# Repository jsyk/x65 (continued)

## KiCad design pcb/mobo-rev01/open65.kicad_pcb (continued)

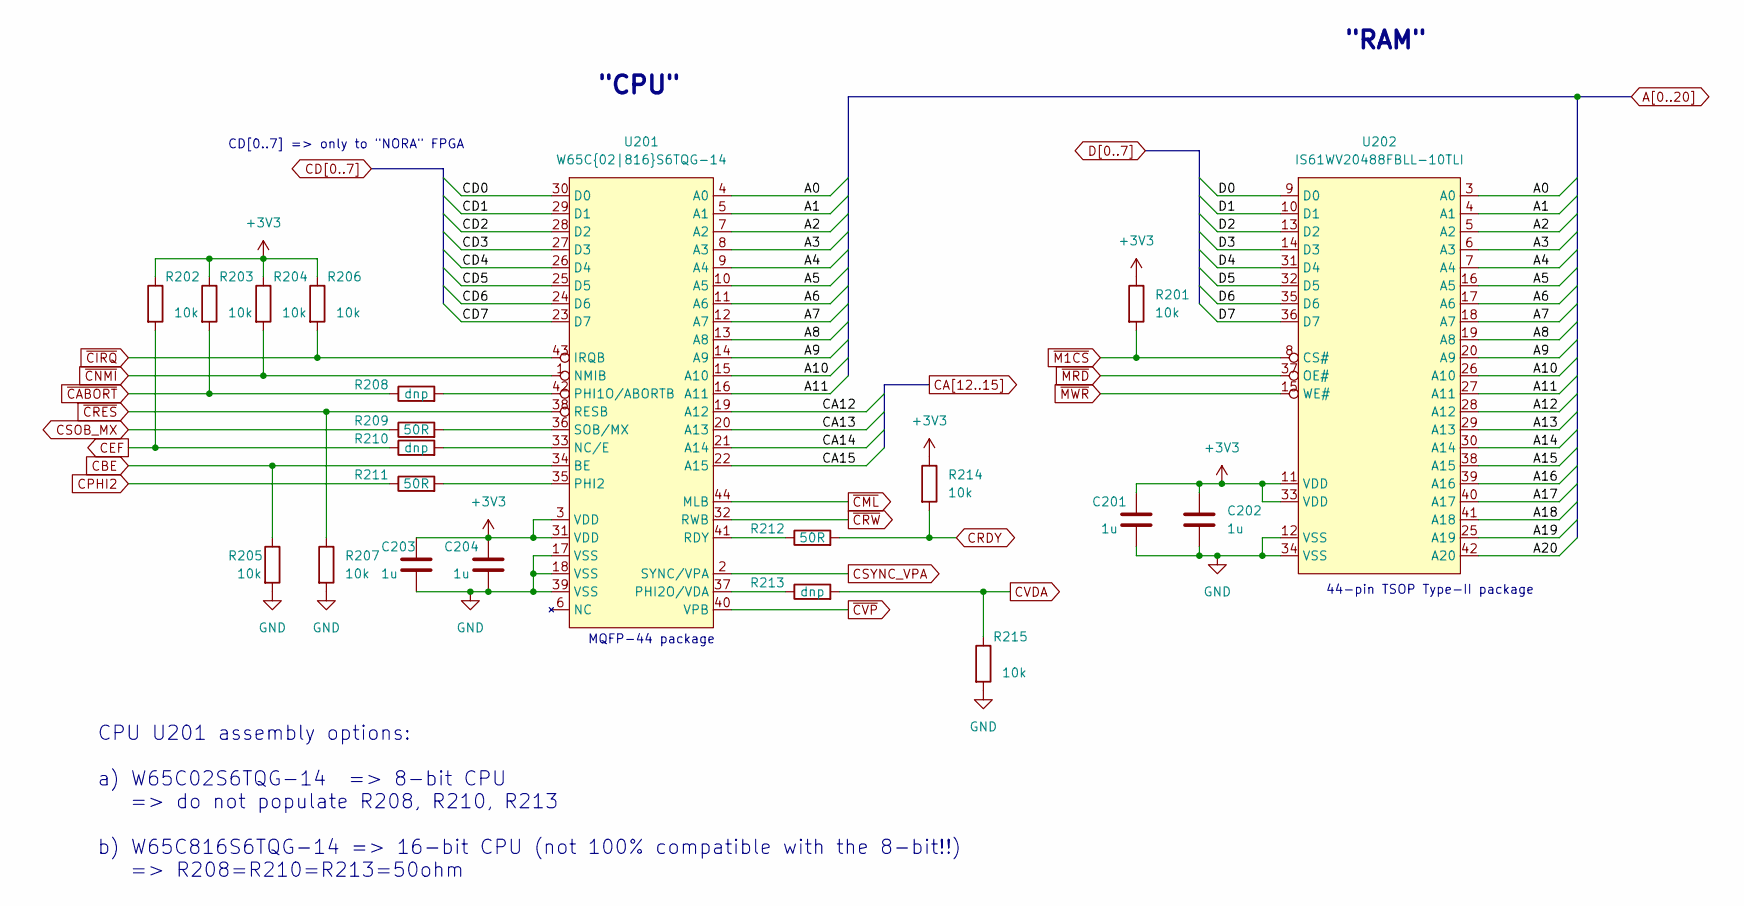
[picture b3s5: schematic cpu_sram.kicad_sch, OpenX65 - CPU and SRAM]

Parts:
C201, C202, C203, C204: 1u; C_0603_1608Metric_Pad1.08x0.95mm_HandSolder
R201, R202, R203, R204, R205, R206, R207, R214, R215: 10k; R_0603_1608Metric_Pad0.98x0.95mm_HandSolder
R208, R210, R213: dnp; R_0603_1608Metric_Pad0.98x0.95mm_HandSolder
R209, R211, R212: 50R; R_0603_1608Metric_Pad0.98x0.95mm_HandSolder
U201: W65C{02|816}S6TQG-14; MQFP-44_10x10mm_P0.8mm
U202: IS61WV20488FBLL-10TLI; TSOP-II-44_10.16x18.41mm_P0.8mm

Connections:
+3V3: C201.1, C202.1, C203.1, C204.1, R201.1, R202.1, R203.1, R204.1, R206.1, R214.1, U201.3 (VDD), U201.31 (VDD), U202.11 (VDD), U202.33 (VDD); also elsewhere on the board
A0: U201.4 (A0), U202.3 (A0); also elsewhere on the board
A1: U201.5 (A1), U202.4 (A1); also elsewhere on the board
A2: U201.7 (A2), U202.5 (A2); also elsewhere on the board
A3: U201.8 (A3), U202.6 (A3); also elsewhere on the board
A4: U201.9 (A4), U202.7 (A4); also elsewhere on the board
A5: U201.10 (A5), U202.16 (A5); also elsewhere on the board
A6: U201.11 (A6), U202.17 (A6); also elsewhere on the board
A7: U201.12 (A7), U202.18 (A7); also elsewhere on the board
A8: U201.13 (A8), U202.19 (A8); also elsewhere on the board
A9: U201.14 (A9), U202.20 (A9); also elsewhere on the board
A10: U201.15 (A10), U202.26 (A10); also elsewhere on the board
A11: U201.16 (A11), U202.27 (A11); also elsewhere on the board
A12: U202.28 (A12); also elsewhere on the board
A13: U202.29 (A13); also elsewhere on the board
A14: U202.30 (A14); also elsewhere on the board
A15: U202.38 (A15); also elsewhere on the board
A16: U202.39 (A16); also elsewhere on the board
A17: U202.40 (A17); also elsewhere on the board
A18: U202.41 (A18); also elsewhere on the board
A19: U202.25 (A19); also elsewhere on the board
A20: U202.42 (A20); also elsewhere on the board
CA12: U201.19 (A12); also elsewhere on the board
CA13: U201.20 (A13); also elsewhere on the board
CA14: U201.21 (A14); also elsewhere on the board
CA15: U201.22 (A15); also elsewhere on the board
CBE: R205.1, U201.34 (BE); also elsewhere on the board
CD0: U201.30 (D0); also elsewhere on the board
CD1: U201.29 (D1); also elsewhere on the board
CD2: U201.28 (D2); also elsewhere on the board
CD3: U201.27 (D3); also elsewhere on the board
CD4: U201.26 (D4); also elsewhere on the board
CD5: U201.25 (D5); also elsewhere on the board
CD6: U201.24 (D6); also elsewhere on the board
CD7: U201.23 (D7); also elsewhere on the board
CEF: R202.2, R210.1; also elsewhere on the board
CPHI2: R211.1; also elsewhere on the board
CRDY: R212.2, R214.2; also elsewhere on the board
CSOB_MX: R209.1; also elsewhere on the board
CSYNC_VPA: U201.2 (SYNC/VPA); also elsewhere on the board
CVDA: R213.2, R215.1; also elsewhere on the board
D0: U202.9 (D0); also elsewhere on the board
D1: U202.10 (D1); also elsewhere on the board
D2: U202.13 (D2); also elsewhere on the board
D3: U202.14 (D3); also elsewhere on the board
D4: U202.31 (D4); also elsewhere on the board
D5: U202.32 (D5); also elsewhere on the board
D6: U202.35 (D6); also elsewhere on the board
D7: U202.36 (D7); also elsewhere on the board
GND: C201.2, C202.2, C203.2, C204.2, R205.2, R207.2, R215.2, U201.17 (VSS), U201.18 (VSS), U201.39 (VSS), U202.12 (VSS), U202.34 (VSS); also elsewhere on the board
unnamed: R208.2, U201.42 (PHI1O/ABORTB)
unnamed: R209.2, U201.36 (SOB/MX)
unnamed: R210.2, U201.33 (NC/E)
unnamed: R211.2, U201.35 (PHI2)
unnamed: R212.1, U201.41 (RDY)
unnamed: R213.1, U201.37 (PHI2O/VDA)
~CABORT: R203.2, R208.1; also elsewhere on the board
~CIRQ: R206.2, U201.43 (IRQB); also elsewhere on the board
~CML: U201.44 (MLB); also elsewhere on the board
~CNMI: R204.2, U201.1 (NMIB); also elsewhere on the board
~CRES: R207.1, U201.38 (RESB); also elsewhere on the board
~CRW: U201.32 (RWB); also elsewhere on the board
~CVP: U201.40 (VPB); also elsewhere on the board
~M1CS: R201.2, U202.8 (CS#); also elsewhere on the board
~MRD: U202.37 (OE#); also elsewhere on the board
~MWR: U202.15 (WE#); also elsewhere on the board

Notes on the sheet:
CD[0..7] => only to "NORA" FPGA
"CPU"
CPU U201 assembly options: a) W65C02S6TQG-14 => 8-bit CPU => do not populate R208, R210, R213 b) W65C816S6TQG-14 => 16-bit CPU (not 100% compatible with the 8-bit!!) => R208=R210=R213=50ohm
44-pin TSOP Type-II package
MQFP-44 package
"RAM"

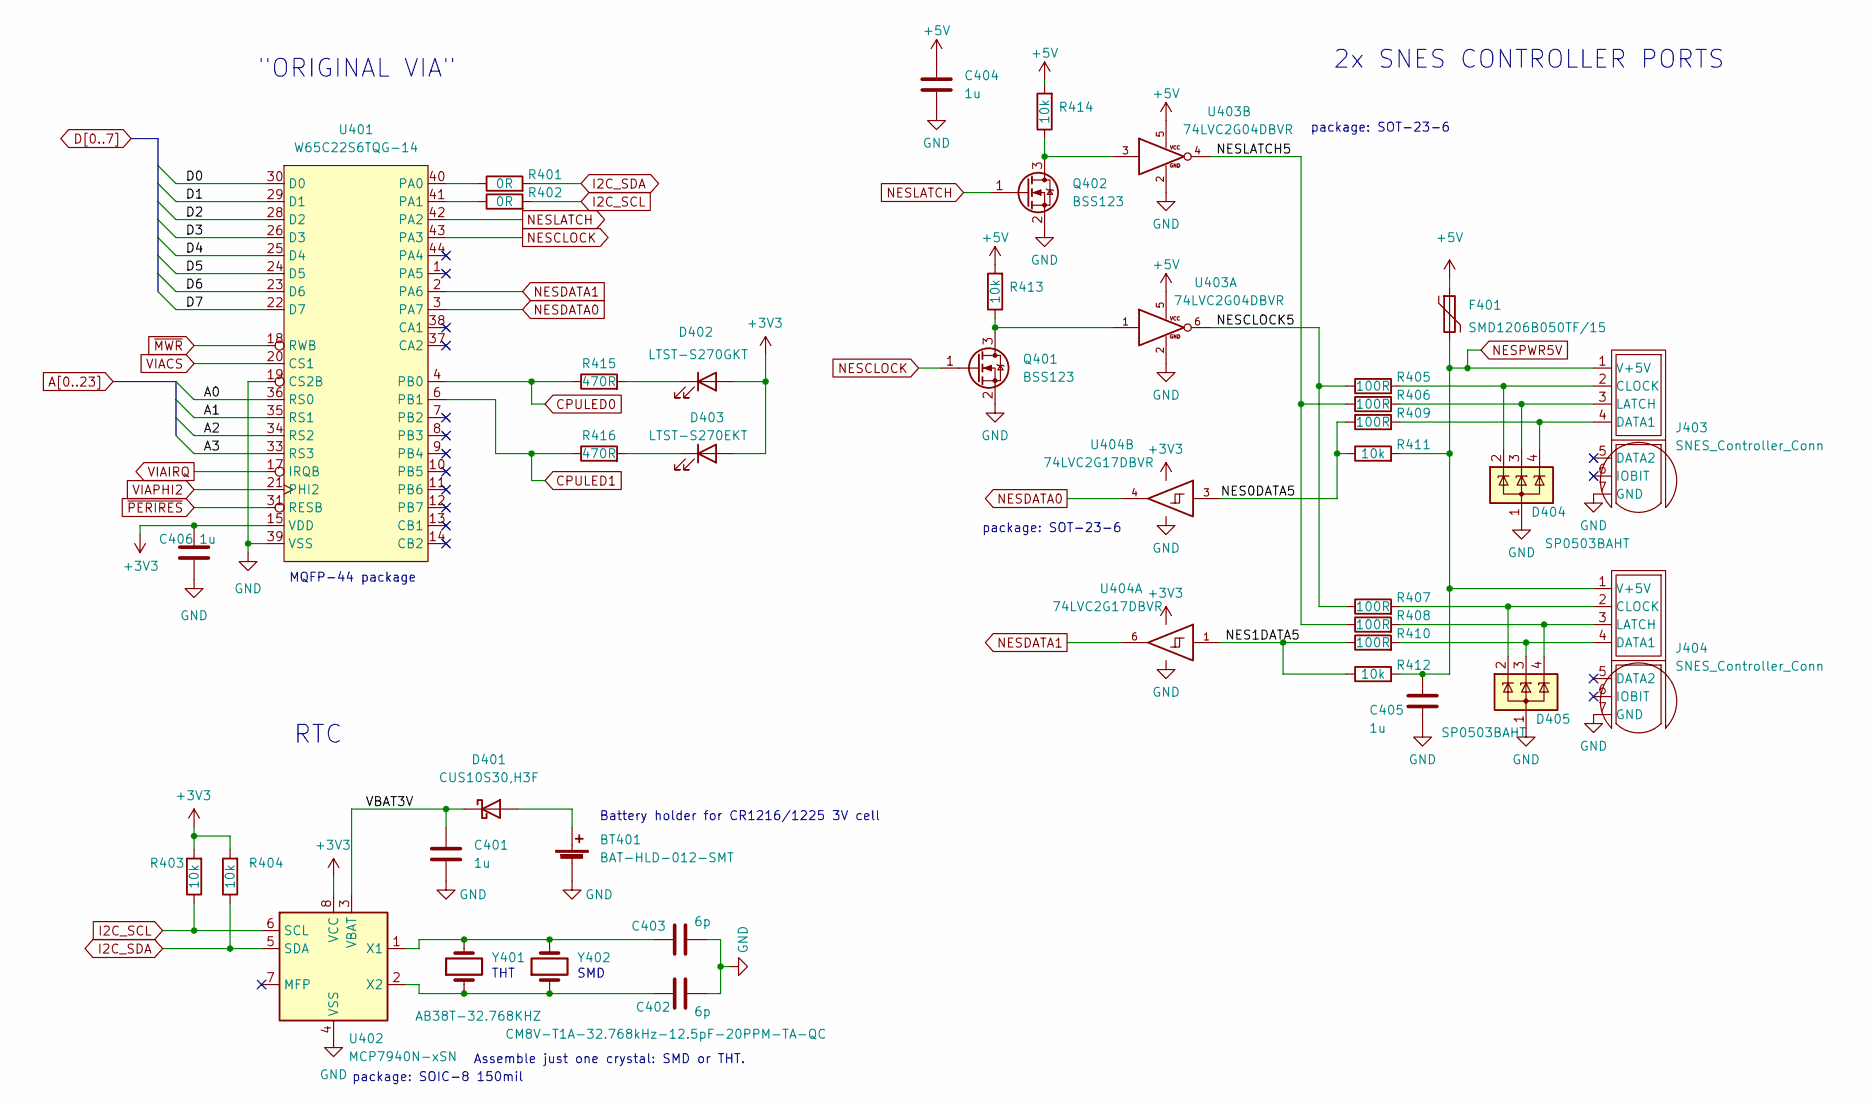
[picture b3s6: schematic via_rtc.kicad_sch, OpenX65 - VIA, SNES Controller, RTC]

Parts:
BT401: BAT-HLD-012-SMT; BatteryHolder_LINX_BAT-HLD-012-SMT
C401, C404, C405, C406: 1u; C_0603_1608Metric_Pad1.08x0.95mm_HandSolder
C402, C403: 6p; C_0603_1608Metric_Pad1.08x0.95mm_HandSolder
D401: CUS10S30,H3F; D_SOD-323_HandSoldering
D402: LTST-S270GKT; LED_0603_1608Metric_Pad1.05x0.95mm_HandSolder
D403: LTST-S270EKT; LED_0603_1608Metric_Pad1.05x0.95mm_HandSolder
D404, D405: SP0503BAHT; SOT-143
F401: SMD1206B050TF/15; Fuse_1206_3216Metric_Pad1.42x1.75mm_HandSolder
J403, J404: SNES_Controller_Conn; SNES_Controller_Conn_7p_90deg_P1Left
Q401, Q402: BSS123; SOT-23
R401, R402: 0R; R_0603_1608Metric_Pad0.98x0.95mm_HandSolder
R403, R404, R411, R412, R413, R414: 10k; R_0603_1608Metric_Pad0.98x0.95mm_HandSolder
R405, R406, R407, R408, R409, R410: 100R; R_0603_1608Metric_Pad0.98x0.95mm_HandSolder
R415, R416: 470R; R_0603_1608Metric_Pad0.98x0.95mm_HandSolder
U401: W65C22S6TQG-14; MQFP-44_10x10mm_P0.8mm
U402: MCP7940N-xSN; SO-8_3.9x4.9mm_P1.27mm
U403: 74LVC2G04DBVR; SOT-23-6_Handsoldering
U404: 74LVC2G17DBVR; SOT-23-6_Handsoldering
Y401: AB38T-32.768KHZ; Crystal_C38-LF_D3.0mm_L8.0mm_Horizontal
Y402: CM8V-T1A-32.768kHz-12.5pF-20PPM-TA-QC; Crystal_SMD_MicroCrystal_CC8V-T1A-2Pin_2.0x1.2mm_HandSolder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

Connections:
+3V3: C406.1, D402.2 (A), D403.2 (A), R403.2, R404.2, U401.15 (VDD), U402.8 (VCC), U404.5 (VCC); also elsewhere on the board
+5V: C404.1, F401.1, R413.2, R414.2, U403.5; also elsewhere on the board
/VIA, RTC, SNES/NES0DATA5: R409.1, R411.1, U404.3
/VIA, RTC, SNES/NES1DATA5: R410.1, R412.1, U404.1
/VIA, RTC, SNES/NESCLOCK5: R405.1, R407.1, U403.6
/VIA, RTC, SNES/NESLATCH5: R406.1, R408.1, U403.4
/VIA, RTC, SNES/VBAT3V: C401.1, D401.1 (K), U402.3 (VBAT)
A0: U401.36 (RS0); also elsewhere on the board
A1: U401.35 (RS1); also elsewhere on the board
A2: U401.34 (RS2); also elsewhere on the board
A3: U401.33 (RS3); also elsewhere on the board
CPULED0: R415.1, U401.4 (PB0); also elsewhere on the board
CPULED1: R416.1, U401.6 (PB1); also elsewhere on the board
D0: U401.30 (D0); also elsewhere on the board
D1: U401.29 (D1); also elsewhere on the board
D2: U401.28 (D2); also elsewhere on the board
D3: U401.26 (D3); also elsewhere on the board
D4: U401.25 (D4); also elsewhere on the board
D5: U401.24 (D5); also elsewhere on the board
D6: U401.23 (D6); also elsewhere on the board
D7: U401.22 (D7); also elsewhere on the board
GND: BT401.2 (-), C401.2, C402.2, C403.2, C404.2, C405.2, C406.2, D404.1 (A), D405.1 (A), J403.7 (GND), J404.7 (GND), Q401.2 (S), Q402.2 (S), U401.19 (CS2B), U401.39 (VSS), U402.4 (VSS), U403.2, U404.2 (GND); also elsewhere on the board
I2C_SCL: R402.2, R403.1, U402.6 (SCL); also elsewhere on the board
I2C_SDA: R401.2, R404.1, U402.5 (SDA); also elsewhere on the board
NESCLOCK: Q401.1 (G), U401.43 (PA3); also elsewhere on the board
NESDATA0: U401.3 (PA7), U404.4; also elsewhere on the board
NESDATA1: U401.2 (PA6), U404.6; also elsewhere on the board
NESLATCH: Q402.1 (G), U401.42 (PA2); also elsewhere on the board
NESPWR5V: C405.1, F401.2, J403.1 (V+5V), J404.1 (V+5V), R411.2, R412.2; also elsewhere on the board
unnamed: BT401.1 (+), D401.2 (A)
unnamed: C402.1, U402.2 (X2), Y401.1, Y402.1
unnamed: C403.1, U402.1 (X1), Y401.2, Y402.2
unnamed: D402.1 (K), R415.2
unnamed: D403.1 (K), R416.2
unnamed: D404.2 (K), J403.2 (CLOCK), R405.2
unnamed: D404.3 (K), J403.3 (LATCH), R406.2
unnamed: D404.4 (K), J403.4 (DATA1), R409.2
unnamed: D405.2 (K), J404.2 (CLOCK), R407.2
unnamed: D405.3 (K), J404.4 (DATA1), R410.2
unnamed: D405.4 (K), J404.3 (LATCH), R408.2
unnamed: Q401.3 (D), R413.1, U403.1
unnamed: Q402.3 (D), R414.1, U403.3
unnamed: R401.1, U401.40 (PA0)
unnamed: R402.1, U401.41 (PA1)
VIACS: U401.20 (CS1); also elsewhere on the board
VIAIRQ: U401.17 (IRQB); also elsewhere on the board
VIAPHI2: U401.21 (PHI2); also elsewhere on the board
~MWR: U401.18 (RWB); also elsewhere on the board
~PERIRES: U401.31 (RESB); also elsewhere on the board

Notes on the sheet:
RTC
SMD
MQFP-44 package
"ORIGINAL VIA"
Assemble just one crystal: SMD or THT.
2x SNES CONTROLLER PORTS
package: SOT-23-6
Battery holder for CR1216/1225 3V cell
package: SOIC-8 150mil
THT

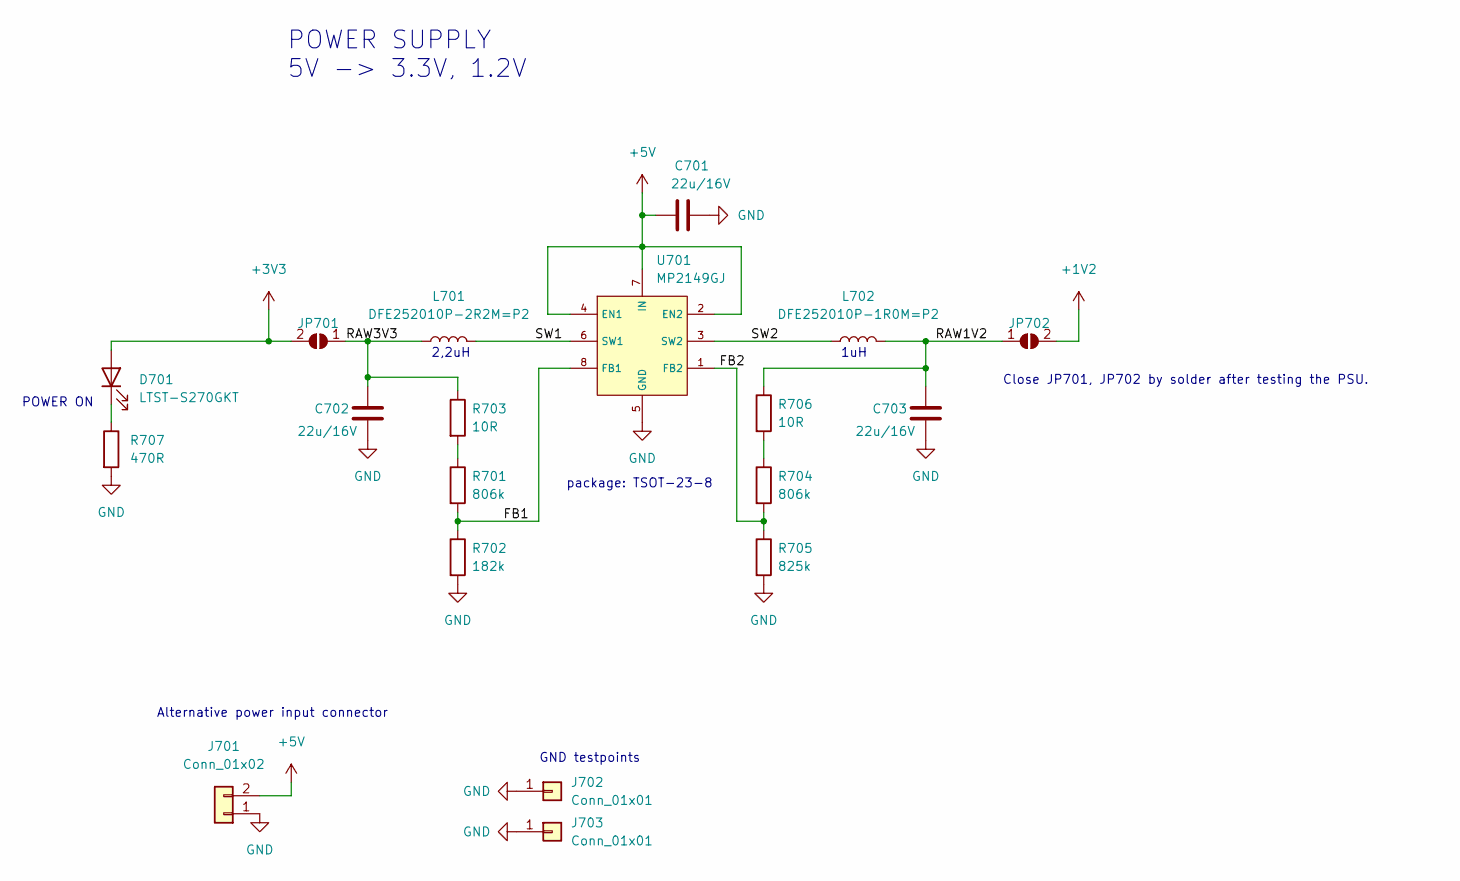
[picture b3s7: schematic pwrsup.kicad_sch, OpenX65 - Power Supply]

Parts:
C701, C702, C703: 22u/16V; C_0805_2012Metric_Pad1.18x1.45mm_HandSolder
D701: LTST-S270GKT; LED_0603_1608Metric_Pad1.05x0.95mm_HandSolder
J701: Conn_01x02; PinHeader_1x02_P2.54mm_Vertical
J702, J703: Conn_01x01; PinHeader_1x01_P2.54mm_Vertical
JP701, JP702: SolderJumper_2_Bridged; SolderJumper-2_P1.3mm_Open_RoundedPad1.0x1.5mm
L701: DFE252010P-2R2M=P2; L_1008_2520Metric_Pad1.43x2.20mm_HandSolder
L702: DFE252010P-1R0M=P2; L_1008_2520Metric_Pad1.43x2.20mm_HandSolder
R701, R704: 806k; R_0603_1608Metric_Pad0.98x0.95mm_HandSolder
R702: 182k; R_0603_1608Metric_Pad0.98x0.95mm_HandSolder
R703, R706: 10R; R_0603_1608Metric_Pad0.98x0.95mm_HandSolder
R705: 825k; R_0603_1608Metric_Pad0.98x0.95mm_HandSolder
R707: 470R; R_0603_1608Metric_Pad0.98x0.95mm_HandSolder
U701: MP2149GJ; TSOT-23-8_HandSoldering

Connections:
+1V2: JP702.2 (B); also elsewhere on the board
+3V3: D701.2 (A), JP701.2 (B); also elsewhere on the board
+5V: C701.1, J701.2, U701.2 (EN2), U701.4 (EN1), U701.7 (IN); also elsewhere on the board
/Power Supply/FB1: R701.2, R702.1, U701.8 (FB1)
/Power Supply/FB2: R704.2, R705.1, U701.1 (FB2)
/Power Supply/RAW1V2: C703.2, JP702.1 (A), L702.2, R706.1
/Power Supply/RAW3V3: C702.2, JP701.1 (A), L701.1, R703.1
/Power Supply/SW1: L701.2, U701.6 (SW1)
/Power Supply/SW2: L702.1, U701.3 (SW2)
GND: C701.2, C702.1, C703.1, J701.1, J702.1, J703.1, R702.2, R705.2, R707.2, U701.5 (GND); also elsewhere on the board
unnamed: D701.1 (K), R707.1
unnamed: R701.1, R703.2
unnamed: R704.1, R706.2

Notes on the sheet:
1uH
2,2uH
POWER ON
POWER SUPPLY 5V -> 3.3V, 1.2V
GND testpoints
package: TSOT-23-8
Close JP701, JP702 by solder after testing the PSU.
Alternative power input connector

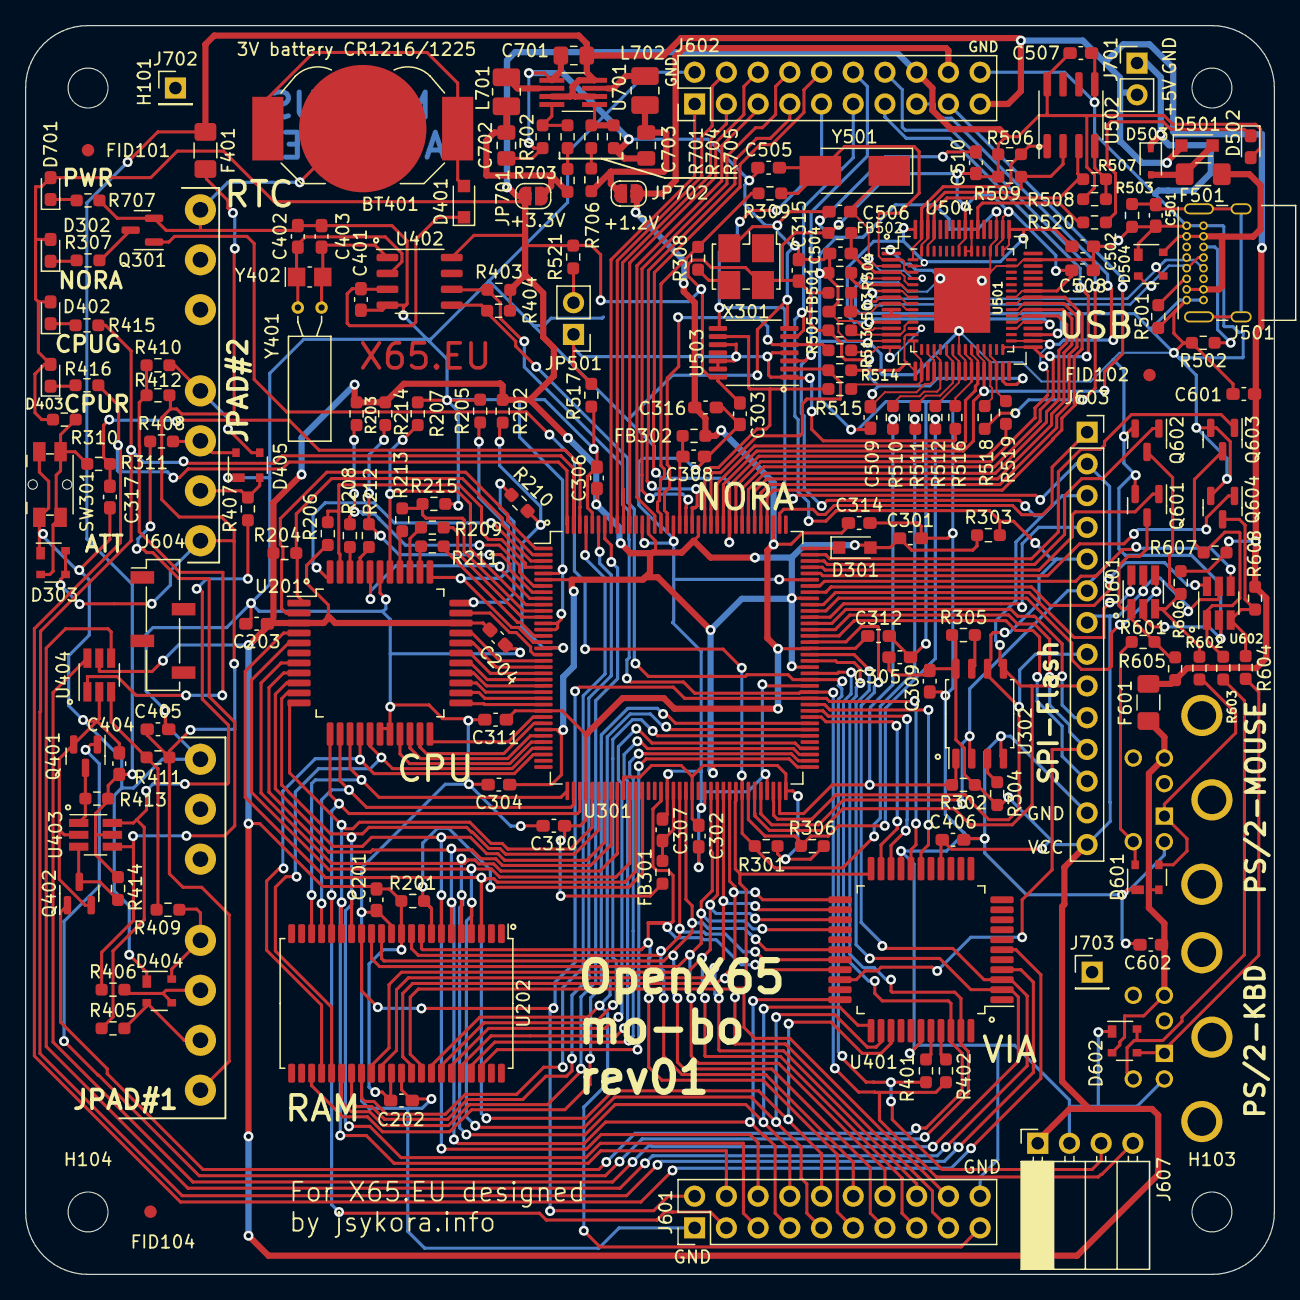
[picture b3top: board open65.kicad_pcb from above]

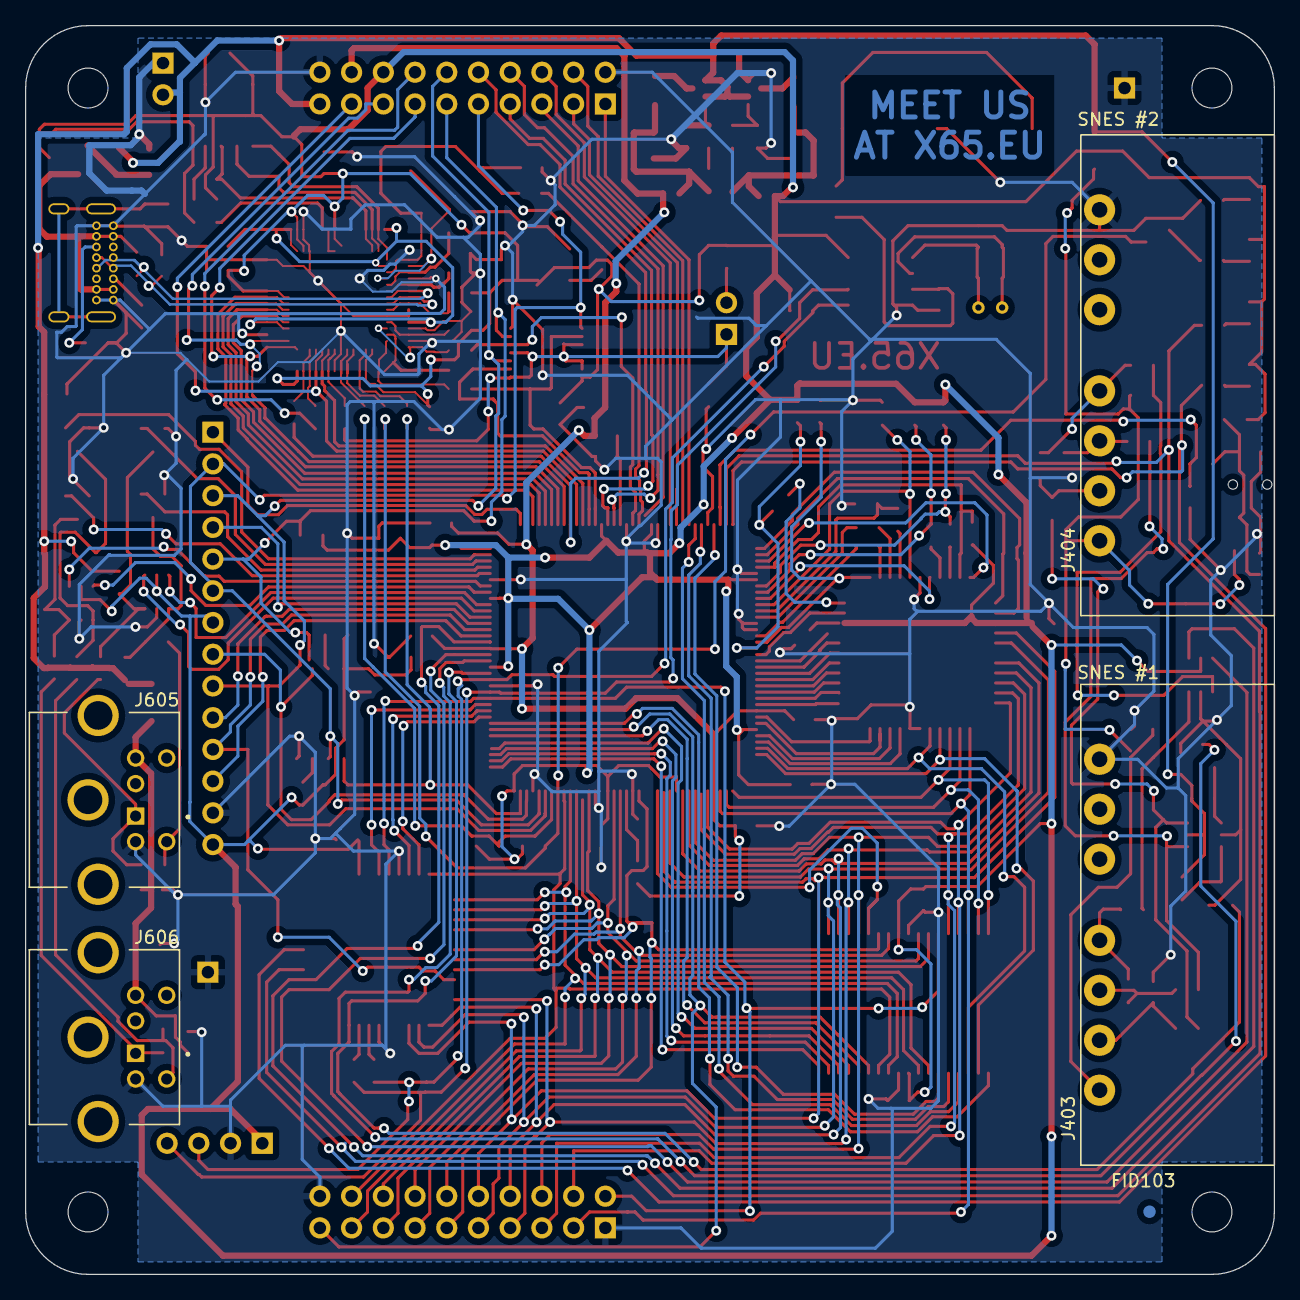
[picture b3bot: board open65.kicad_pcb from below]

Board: 2 copper layers, 100.0 x 100.0 mm, 195 parts (5 on the bottom side), 199 nets.

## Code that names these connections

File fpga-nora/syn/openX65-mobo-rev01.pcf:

# OpenX65 motherboard rev 01

#
# Bank 3
#   Pins 1 - 34
#
set_io CSYNC_VPA    1
set_io CNMIn        2
set_io CMLn         3
set_io CIRQn        4
set_io CABORTn      7
set_io CRDY         8
set_io CVPn         9
set_io CRESn        10
set_io CVDA         11
set_io CSOB_MX      12
set_io CPHI2        15
set_io CBE          16
set_io CEF          17
set_io CRWn         18
set_io CD[0]          19  
set_io CD[1]          20
set_io CD[2]          21
set_io CD[3]          22
set_io CD[4]          23
set_io CD[5]          24
set_io CD[6]          25
set_io CD[7]          26
set_io CA[15]         28
set_io CA[14]         29
set_io CA[13]         31
set_io CA[12]         32
set_io MAL[11]          33
set_io MAL[10]          34

#
# Bank 2
#   Pins 37 - 64
#
set_io MAL[9]           37
set_io MAL[8]           38
set_io MAL[7]           39
set_io MAL[6]           41
set_io MAL[5]           42
set_io MAL[4]           43
set_io MAL[3]           44
set_io MAL[2]           45
set_io MAL[1]           47
set_io MAL[0]           48
set_io M1CSn        49
set_io MD[0]           52
set_io MD[1]           55
set_io MD[2]           56
set_io MD[3]           60
set_io MD[4]           61
set_io MD[5]           62
set_io MD[6]           63
set_io MD[7]           64


#
# Bank 1
#   Pins 73 - 107
#
set_io MAH[20]          73
set_io MAH[18]          74
set_io MAH[17]          75
set_io MAH[16]          76
set_io MAH[15]          78
set_io MRDn         79
set_io MAH[19]          80
#set_io VIAPHI2      81
#set_io VIACS        82
#set_io VIAIRQ       83
set_io MWRn         84
set_io I2C_SCL      85
set_io I2C_SDA      87
set_io NESLATCH     88
set_io NESCLOCK     90
set_io NESDATA1     91
set_io NESDATA0     93
set_io ILICSn       94
set_io PERIRESn     95
set_io ILIDC        96
set_io TCSn         97
set_io PS2M_DATA    98
set_io PS2M_CLK     99
set_io PS2K_CLK     101
set_io PS2K_DATA    102
set_io PS2K_DATADR  104
set_io PS2M_CLKDR   105
set_io PS2M_DATADR  106
set_io PS2K_CLKDR   107

#
# Bank 0
#   Pins 110 - 144
#
set_io CPUTYPE02    110
set_io UART_CTS     112
set_io UART_RTS     113
set_io UART_TX      114
set_io UART_RX      115
set_io VERADONE     116
set_io VERARSTn     117
set_io VERAFCSn     118
set_io ICD2VERAROM  119
set_io ICD_CSn      120
set_io ICD_MOSI     121
set_io ICD_MISO     122
set_io VCS2n        124
set_io VIRQn        125
set_io ICD_SCK      128
set_io FPGACLK      129
set_io VCS1n        130
set_io AUDIO_LRCK   134
set_io VCS0n        135
set_io AUDIO_DATA   136
set_io AUDIO_BCK    137
set_io MAH[12]          138
set_io MAH[13]          139
set_io MAH[14]          141
set_io ATTBTN       142
set_io CPULED0      143
set_io CPULED1      144


#
# Bank SPI
#
set_io FMOSI        67
set_io FMISO        68
set_io FSCK         70
set_io FLASHCSn     71

# set_io CDONE        65

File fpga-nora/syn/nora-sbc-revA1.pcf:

# X65 SBC rev.A1

#
# Bank 3
#   Pins 1 - 34
#
set_io CSYNC_VPA    1
set_io CNMIn        2
set_io CMLn         3
set_io CIRQn        4
set_io CABORTn      7
set_io CRDY         8
set_io CVPn         9
set_io CRESn        10
set_io CVDA         11
set_io CSOB_MX      12
set_io CPHI2        15
set_io CBE          16
set_io CEF          17
set_io CRWn         18
set_io CD[0]          19  
set_io CD[1]          20
set_io CD[2]          21
set_io CD[3]          22
set_io CD[4]          23
set_io CD[5]          24
set_io CD[6]          25
set_io CD[7]          26
set_io CA[15]         28
set_io CA[14]         29
set_io CA[13]         31
set_io CA[12]         32
set_io MAL[11]          33
set_io MAL[10]          34

#
# Bank 2
#   Pins 37 - 64
#
set_io MAL[9]           37
set_io MAL[8]           38
set_io MAL[7]           39
set_io MAL[6]           41
set_io MAL[5]           42
set_io MAL[4]           43
set_io MAL[3]           44
set_io MAL[2]           45
set_io MAL[1]           47
set_io MAL[0]           48
set_io M1CSn        49
set_io MD[0]           52
set_io MD[1]           55
set_io MD[2]           56
set_io MD[3]           60
set_io MD[4]           61
set_io MD[5]           62
set_io MD[6]           63
set_io MD[7]           64


#
# Bank 1
#   Pins 73 - 107
#
set_io MAH[20]          73
set_io MAH[18]          74
set_io MAH[17]          75
set_io MAH[16]          76
set_io MAH[15]          78
set_io MRDn             79
set_io MAH[19]          80
set_io UE_IRQn          81
set_io PS2M_DATA        82
set_io PS2M_CLK         83
set_io MWRn         84
set_io I2C_SCL      85
set_io I2C_SDA      87
set_io EIRQn        88
set_io AIRQn        90
set_io VIRQn        91
set_io ACS1n        93
set_io VCS0n        94
set_io UE_CS3n      95
set_io UE_SCK       96
set_io UE_CSn       97
set_io UE_MISO      98
set_io UE_MOSI      99
set_io UE_SCL       101
set_io UE_SDA       102
set_io UE_TXD       104
set_io UE_RXD       105
set_io PS2K_DATA    106
set_io PS2K_CLK     107

#
# Bank 0
#   Pins 110 - 144
#
set_io CPUTYPE02    110
set_io UART_RTS     112
set_io UART_CTS     113
set_io UART_TX      114
set_io UART_RX      115
set_io VEAURADONE   116
set_io VERARSTn     117
set_io ERSTn        118
set_io ARSTn        119
set_io ICD_CSn      120
set_io ICD_MOSI     121
set_io ICD_MISO     122
set_io ECS2n        124
set_io DIPLED0      125
set_io ICD_SCK      128
set_io FPGACLK      129
set_io NESDATA0     130
set_io NESDATA1     134
set_io NESCLOCK     135
set_io NESLATCH     136
set_io DIPLED1      137
set_io MAH[12]          138
set_io MAH[13]          139
set_io MAH[14]          141
set_io ATTBTN       142
set_io CPULED0      143
set_io CPULED1      144


#
# Bank SPI
#
set_io FMOSI        67
set_io FMISO        68
set_io FSCK         70
set_io FLASHCSn     71

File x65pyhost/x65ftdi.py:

import pyftdi.spi

# Documenation pyftdi: SPI API
# https://eblot.github.io/pyftdi/api/spi.html

class X65Ftdi:
    # Definitions of pins of the FTDI FT2232H in the OpenX65 motherboard.
    # // bit masks of the signals on ADBUSx (low byte)
    PIN_SCK  = 0x0001
    PIN_MOSI = 0x0002
    PIN_MISO = 0x0004
    PIN_NORAFCSN = 0x0010         # // ADBUS4 (GPIOL0) (FLASHCSN)
    PIN_NORADONE = 0x0040           # // ADBUS6 (GPIOL2)
    PIN_NORARSTN = 0x0080         # // ADBUS7 (GPIOL3)
    # // bit masks of the signals on ACBUSx (high byte)
    PIN_ICD2NORAROM = 0x0100			#// ACBUS0
    PIN_ICDCSN = 0x0200			        #// ACBUS1
    PIN_AURARSTN = 0x0400		        #// ACBUS2 (was ICD2VERAROM)
    PIN_AURAFCSN = 0x0800			    #// ACBUS3 (was VERA2FCS)
    PIN_VERAFCSN = 0x1000			    #// ACBUS4
    PIN_CPUTYPE02 = 0x2000              #// ACBUS5
    PIN_VAFCDONE = 0x4000			    #// ACBUS6 (was VERADONE)
    PIN_VERARSTN = 0x8000			    #// ACBUS7

    PINS_ALL = PIN_NORAFCSN | PIN_NORADONE | PIN_NORARSTN | PIN_ICD2NORAROM | PIN_ICDCSN | PIN_AURARSTN | PIN_AURAFCSN | PIN_VERAFCSN | PIN_VAFCDONE | PIN_VERARSTN | PIN_CPUTYPE02

    def __init__(self, url = 'ftdi://ftdi:2232/1', log_file_name=None):
        if url is not None:
            self.openFtdi(url)
        # open log file?
        if log_file_name is not None:
            self.logf = open(log_file_name, 'a')
            self.logf.write('\n\nStart of log\n')
        else:
            self.logf = None

    def openFtdi(self, url = 'ftdi://ftdi:2232/1'):
        # Instantiate a SPI controller
        self.spi = pyftdi.spi.SpiController()

        # Configure the first interface (IF/1) of the first FTDI device as a
        # SPI master
        self.spi.configure(url)

        # Get a SPI port to a SPI slave w/ /CS on A*BUS3 and SPI mode 0 @ 6MHz
        self.slave = self.spi.get_port(cs=0, freq=1E6, mode=0)

        # Get GPIO port to manage extra pins, use A*BUS4 as GPO, A*BUS4 as GPI
        self.gpio = self.spi.get_gpio()

        self.pinout_idle()

    # // configure the high-byte (ACBUSx) to route SPI to the ICD,
    # // and keep ICD high (deselect).
    def pinout_idle(self):
        # for all GPIOs, configure just ICD2NORAROM and ICDCSN as outputs
        self.gpio.set_direction(X65Ftdi.PINS_ALL,
                            X65Ftdi.PIN_ICD2NORAROM | X65Ftdi.PIN_ICDCSN)
        # // drive low ICD2NORAROM (this unroutes SPI to flash),
        # // drive high ICDCSN, all others are IN.
        self.gpio.write(X65Ftdi.PIN_ICDCSN)


    # // ICD chip select assert
    # // should only happen while ICD2NORAROM=Low
    def icd_chip_select(self):
        # // drive low ICD2NORAROM (this unroutes SPI to flash),
        # // drive low ICDCSN to activate the ICD
        self.gpio.write(0)
        if self.logf is not None:
            self.logf.write('SELECT\n')
        # mpsse_set_gpio_high(VERA2FCSN | VERAFCSN | VERADONE | VERARSTN, 
        # 			ICD2NORAROM | ICDCSN);

    # // ICD chip select deassert
    def icd_chip_deselect(self):
        # // drive low ICD2NORAROM (this unroutes SPI to flash),
        # // drive high ICDCSN to de-activate the ICD
        self.gpio.write(X65Ftdi.PIN_ICDCSN)
        if self.logf is not None:
            self.logf.write('DESEL\n')
        # mpsse_set_gpio_high(ICDCSN | VERA2FCSN | VERAFCSN | VERADONE | VERARSTN, 
        # 			ICD2NORAROM | ICDCSN);

    def spiexchange(self, out, readlen):
        if self.logf is not None:
            self.logf.write('  EX.out {}\n'.format( ''.join('{:02x} '.format(x) for x in out) ))
        read = self.slave.exchange(out, readlen, start=False, stop=False, duplex=True)
        if self.logf is not None:
            self.logf.write('  EX.inp {}\n'.format( ''.join('{:02x} '.format(x) for x in read) ))
        return read

    def spiwriteonly(self, out):
        if self.logf is not None:
            self.logf.write('  WO.out {}\n'.format( ''.join('{:02x} '.format(x) for x in out) ))
        self.slave.write(out,  start=False, stop=False)

    # Read the CPUTYPE02 signal available on FTDI pin ACBUS5.
    # Returns TRUE in case of 65C02, and FALSE in case of 65C816 CPU is installed on the target board.
    def is_cputype02(self):
        return (self.gpio.read() & X65Ftdi.PIN_CPUTYPE02) != 0

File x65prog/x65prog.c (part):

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};

// bit masks of the signals on ACBUSx
#define ICD2NORAROM 		0x01			// ACBUS0
#define ICDCSN				0x02			// ACBUS1
#define AURARSTN			0x04			// ACBUS2
#define AURAFCS				0x08			// ACBUS3
#define VERAFCS				0x10			// ACBUS4
#define VERAAURADONE		0x40			// ACBUS6
#define VERARSTN			0x80			// ACBUS7

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	uint8_t direction = 0x03;

	if (!cs_b) {
		// ADBUS4 (GPIOL0) = FLASHCSN for NORA
		direction |= 0x10;		// set to output mode, will drive 0
	}

	if (!creset_b) {
		// ADBUS7 (GPIOL3) = NORARSTN
		direction |= 0x80;		// set to output mode, will drive 0
	}

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static void set_cs_creset_vera(int cs_b, int creset_b)
{
	// bitmap of GPIO output register values (0/1 drive)
	uint8_t gpio = ICD2NORAROM;
	// bitmap of GPIO direction register values (0=in, 1=out)
	uint8_t direction = 0x03 | ICD2NORAROM | VERAFCS | AURAFCS;

	if (!cs_b) {
		// ADBUS4 (GPIOL0) = VERAFCS for VERA
		// direction |= VERAFCS;		// set to output mode, will drive logic 1
		gpio |= VERAFCS;			// drive HIGH to VERAFCS; this enables the bus-switch U404 on VABO
	}

	if (!creset_b) {
		// ADBUS7 (GPIOL3) = VERARSTN
		direction |= VERARSTN;		// set to output mode, will drive 0
	}

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static void set_cs_creset_aura(int cs_b, int creset_b)
{
	// bitmap of GPIO output register values (0/1 drive)
	uint8_t gpio = ICD2NORAROM;				// drive high ICD2NORAROM, so that FTDI gets to FMOSI/FSCK bus
	// bitmap of GPIO direction register values (0=in, 1=out)
	uint8_t direction = 0x03 | ICD2NORAROM | VERAFCS | AURAFCS;		// drive ICD2NORAROM, VERAFCS, AURAFCS

	if (!cs_b) {
		// ACBUS3) = AURAFCS for AURA
		gpio |= AURAFCS;			// drive HIGH to AURAFCS; this enables the bus-switch U602 on VABO
	}

	if (!creset_b) {
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
static bool get_cdone_nora(void)
{
	// ADBUS6 (GPIOL2) = NORADONE
	return (mpsse_readb_low() & 0x40) != 0;
}

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	// drive high ICD2NORAROM (= ICD2FLASHES), ICDCSN, 
	// drive low AURAFCS, low VERAFCS,
	// keep others as IN.
	mpsse_set_gpio_high(ICD2NORAROM | ICDCSN  | VERAAURADONE | VERARSTN, 
				ICD2NORAROM | ICDCSN | AURAFCS | VERAFCS);
}

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{
	// drive low ICD2NORAROM (this unroutes SPI to flash), 
	// drive high ICDCSN, keep others as IN.
	mpsse_set_gpio_high(ICDCSN | AURAFCS | VERAFCS | VERAAURADONE | VERARSTN, 
				ICD2NORAROM | ICDCSN);
}

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
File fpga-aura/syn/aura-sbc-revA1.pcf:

# OpenX65 VABO rev 01 - AURA FPGA pins

set_io      DB[0]       25
set_io      MWRN        23
set_io      DB[2]       27
set_io      DB[1]       26
set_io      VCS0N       28
set_io      DB[3]       31
set_io      DB[4]       32
set_io      DB[5]       34
set_io      DB[7]       37
set_io      ASYSCLK     35
set_io      DB[6]       36
set_io      SD_SSELN    43
set_io      MUTEN       38
set_io      AURALED     42

# set_io      ARSTN       8     # pin 8 cannot be assigned in UL
set_io      IOCSN       47       # unused in SBC
set_io      AUDIO_BCK   9
set_io      VAUDIO_LRCK 10
set_io      VAUDIO_DATA 11
set_io      VAUDIO_BCK  12
set_io      AB[4]       21
set_io      AB[3]       13
set_io      MRDN        20
set_io      AB[2]       19
set_io      AB[1]       18
set_io      ASPI_MOSI   14
set_io      ASPI_MISO   17
set_io      ASPI_SCK    15
set_io      AFLASH_SSELN    16

set_io      ACS1N       46
set_io      AIRQN       48
set_io      AB[0]       45
set_io      AUDIO_LRCK  4
set_io      AUDIO_DATA  3

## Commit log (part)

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2023-04-11 PCB mobo rev01
2023-04-11 x65prog sources
2023-04-11 FPGA NORA files
2023-04-11 Update gitignore with verilog tmp files
2023-04-13 update gitignore
2023-04-13 NORA: correct timing of WR and other signals
2023-04-13 Add testing pictures from the scope
2023-04-18 Started the video/audio board
2023-04-29 start of pythonic ICD
2023-04-30 Add LED-blink x65 program
2023-05-04 PS2 port can read keyboard scan-codes
2023-05-07 x65prog can r/w the VERA Flash
2023-05-07 pyhost: do-vchartest, do-videotest work fine
2023-05-13 Various updates; I2C slave
2023-05-13 Add some photos
2023-05-13 CX16 is READY.
2023-05-14 Add keyboard FIFO -> kbd input works OK
2023-05-14 New photos, update Address Space
2023-05-15 rom: banktest
2023-05-15 Update docs
2023-05-15 smc: implement ps2k cmd send and status report
    problem: bus controller does not update rambank_nr on CPU write!!!
    after unrelated change in the smc!
2023-05-15 fix verilog undefined wires
    yosis reports undefined wires just as warnings, but then the
    output bitstream fails intermitently... what?
2023-05-15 Readme: describe structure
2023-05-18 doc fix
2023-05-18 verilog fix bit width in arithmetic expr.
2023-05-18 smc: fix arith expr bit-length
2023-05-18 smc: localparams, non-working 2B commands (but the x16 rom runs well)
2023-05-21 bus_controller: fix rambank/rombank write cycle position!!
2023-05-21 Photos: front and rear view with connectors
2023-05-25 rename file X16 -> CX16.txt
2023-05-25 split smc into ps2_kbd_host, add a tb
2023-05-25 add UEXT to the ideas for rev02
2023-05-26 rewrite of smc and ps2_kbd_host, to handle the 2B command; CapsLock now works!
2023-05-26 smc: remove commented out code
2023-05-27 do-videotest: run VRAM memtest
2023-06-02 phaser comments
2023-06-10 fpga code cleanup & stabilization
2023-06-20 Update readme & scm with the latest PCB bringup info
2023-06-20 NORA: add mouse support, not tested at all!
2023-06-21 ps2_kbd_host: report RX FIFO count
2023-06-21 smc: implement mouse buffer; works a bit, but not well.
2023-06-24 nora: ps2 mouse now works!
2023-06-25 smc: cleanup
2023-07-03 bringup notes in scm pdf
2023-07-03 nora: invert the NESCLOCK and NESLATCH since we assembled the 74LVC2G17 buffer
2023-07-05 nora: implement PS2 scancode-to-keycode translation in HW (R43)
2023-07-06 nora: CPU vector pull always from ROMBANK 0
2023-07-08 nora: testbench corrections
2023-07-15 nora: spi master
2023-07-15 Add jt51, but do not integrate yet (it is surprasingly too big!)
2023-07-16 Add bootrom to NORA
2023-07-16 ICD: support poke/dump of the bootrom area
2023-07-22 nora: spi master and host, syregs at 0x9F50 started
2023-07-23 cpustep coloring, spitest
2023-07-29 rom pbl can load CX16 ROM from SPI-Flash
    TBD: hard-coded length and parameters
    TBD: NORA starts in debug-stop by default
2023-07-29 update Address Space table
2023-08-05 doc update
2023-08-11 upd gitignore
2023-08-11 copy of VERA 0.3.1 release from X16Community
    https://github.com/X16Community/vera-module/releases/tag/v0.3.1
2023-08-11 add ROM trampoline code (not used directly, just docu)
2023-08-11 add submodule jsyk/IKAOPM
2023-10-28 Integrate IKAOPM into NORA
2023-10-29 gitignore raw, log
2023-10-30 NORA: fix IKAOPM reset; testbench tb_nore opm audio output works
2023-10-30 Remove submodule jt51, it was replaced by IKAOPM
2023-11-01 x65prog: add AURA flash access
2023-11-02 aura: basic OPM works!!
2023-11-02 nora's ikaopm: switch to compressed channel outputs as recommended
2023-11-02 aura: limit OPM to address 0x9F40-43, and IOCSN at 0x9F4C-4F.
2023-11-03 aura: implement input I2S decoder for VERA sound and mixing to the output
    Aura is now 87% full:
    Info: ICESTORM_LC: 4644/ 5280 87%
    Info: ICESTORM_RAM: 10/ 30 33%
    Info: SB_IO: 30/ 96 31%
    Info: SB_GB: 8/ 8 100%
    Info: ICESTORM_PLL: 0/ 1 0%
2023-11-05 IKAOPM: add USE_BRAM parameter
2023-11-05 remove jt51-based fm2151.v, never worked.
2023-11-05 Move IKAOPM to fpga-aura/IKAOPM_dirty
2023-11-05 IKAOPM: removed testbenches
2023-11-11 Update README - status of bringup
2023-11-11 add doc/aura_fpga_opm.md
2023-11-14 remove IKAOPM_dirty
2023-11-14 Add IKAOPM_ice40 repo
2023-11-14 doc: aura_fpga_opm description
2023-11-14 doc: mention calliope app
2023-11-20 aura updates
2023-11-20 icd: add irq-blocking feature during single-step
2023-11-25 AURA FPGA doc rename, fin version
2023-11-25 nora: add tracebuf.v
2023-11-25 nora: integrate the trace buffer memory
2023-11-25 doc Address Space update with AURA, IO REGS, WIZNET
2023-11-26 add doc/pic/x65-small-blockdiagram.drawio
2023-12-02 IKAOPM: fix syntax error in IKAOPM primitive_sr_bram
2023-12-02 fix do-loadprg.py start address
2023-12-09 update schematic with corrections
2023-12-10 Update readme with link
2023-12-14 doc update and cleanup
2023-12-16 readme: 65c816 works!
2023-12-16 basic support of 65c816 in emulation mode in NORA
2023-12-16 nora: cleanup the M and X flag in case of emulation
2023-12-16 icd_controller: make sure the TX byte is always defined or zeroed
2023-12-16 do-cpustep: handle M, X; add sanity checks for comm errors
2023-12-18 update readme with a link to cpu comparison doc.
2023-12-18 nora: record the Cpu Bank Address in trace buffer; display in do-cpustep.py
2023-12-22 nora: memory map rework to suit 65c816
2023-12-23 ps2 port on the second sample, hack
2023-12-25 support 816 in cpustep.py, testrom run816.s
2023-12-25 nora: reduce CD bus driving to the first 10ns after PHI2=falling
2023-12-26 nora: hack ps2 top-level wiring to work on both boards of rev01 that i have
2023-12-26 bringup: add scope pictures regarding testing of CPU vs NORA data bus clash
2023-12-26 add helloworld in C llvm-mos
2023-12-26 ignore prg files
2023-12-26 testsw: add memtest app
2023-12-28 nora: extend S4H phase by 1cc (20ns) for WIZNET accesses
2023-12-28 testsw: picture of overnight memtest
2023-12-28 doc: updates
2023-12-28 testsw wiznet cleanup
2023-12-28 first isafix experiment with abort handler
2024-01-01 pcb: 3d-step models for speaker, sdcard, ethernet jack
2024-01-01 pcb: new footprints lib x65_footprints
2024-01-01 pcb: add pictures used in sbc schematic
2024-01-03 nora: uart_host with tb, doc: ioregs in progress (with futures :-)
2024-01-06 doc: ioregs update (SMC/PS2)
2024-01-06 pcb: fix footprints based on DRC errors
2024-01-06 pcb sbc: more pcb work
2024-01-07 nora: fix UART HwFlowControl RTS generation
2024-01-13 x65-sbc: pcb done
2024-01-13 remove symlink, it is not effective
2024-01-13 pcb update libs
2024-01-13 sbc schematic pdf rev.A1
2024-01-13 sbc: add schematic link
2024-01-14 gerbers submitted to JLCPCB on 14.1.2024
2024-01-15 nora: prepare PCF for SBC
2024-01-15 nora: rename VCS1 to ACS1 and VCS2 to ECS2
2024-01-17 nora: change ROMBLOCK register to 8bits, PBL is selected just by the MSB
2024-01-17 nora: implement ps2 registers
2024-01-26 nora rom: fix red led blinking
2024-01-26 nora: fix do-cpustep after change in ROMBLOCK bits regarding bootrom
2024-01-27 aura: switch to sbc pin map
2024-01-27 nora: implement via#2 and move leds there, update of pbl
2024-01-27 doc: mem-map, ioregs: ROMBLOCK bit 7 enabled PBL rom
2024-01-28 pyhost: update vera and cpureset scripts
2024-01-28 nora: bus_controller: shorten MWR by 1cc on the left because 85C816 outputs data after CPHI2 rising
2024-01-29 nora bus_controller: extend hold time on the memory data bus past CPHI2 falling, for VERA
2024-02-02 nora: bus_controller: remove 1T-2T-advanced timing, it is not necessary
2024-02-02 baremetal tests: vchartst with font
2024-02-03 nora: fix mouse io in sbc
2024-02-03 nora: fix SNES signals, they are positive logic
2024-02-05 do-vchartest: fix font file path
2024-02-05 baremetal sw: update hello (with ps2 reads), and termdemo
2024-02-05 pcb/sbc: add interactive BOM table
2024-02-10 doc: present the sbc
2024-02-10 nora: add ERSTn signal
2024-02-11 doc: sbc-desktop photo
2024-02-11 doc: update README
2024-02-11 nora: add scratchpad to ioregs at 0x9FF0, for the abort handler isafix
2024-02-11 nora isafix first version
2024-02-11 isafix: use 16-bit regs to get the faulting byte code
2024-02-11 isafix: handle RMB/SMB
2024-02-12 Add SBC revB1
2024-02-12 various updated related to the pcb
2024-02-14 update license year to 2024
2024-02-16 cleanup obsolete files
2024-02-16 update README - emulation
2024-02-17 update READMe and topview picture with labels
2024-02-22 nora icd: implement opcode forcing
2024-02-22 pic icd-blockdiagram
2024-02-25 x65pyhost: add register state reading, just 8-bit for now.
2024-02-26 rename CpuState to CpuRegs, implement 16-bit support
2024-03-02 cpustep: add register readout
2024-03-02 doc: describe register readout in icd-cpureg-readout.md
2024-03-03 doc: update pic in regread
2024-03-03 doc cpureg-read: add conclusion
2024-03-06 icd: add unpack_tracereg
2024-03-08 nora spi_slave: sample before sck rising edge
2024-03-08 x65ftdi lib: add spi-log option
2024-03-09 add step file in kicad_pro
2024-03-09 spi_slave instrumentation to check for bounce via histogram. Results: negative - no bouncing detected.
2024-03-11 icd: cleanup unused code
2024-03-11 add pictures from testing: FTDI SCK problem
2024-03-11 icd: move instruction disassembly in own file
2024-03-11 icd cpustep remove unused code
2024-03-14 x65pyhost add comments
2024-03-16 verilog doc, no code change
2024-03-16 rom-pbl: add debugging option to reset through any ROMBLOCK rom
2024-03-18 move bootrom-pbl, bootrom-blinktest
2024-03-19 bootrom code reorg - add config-pbl.inc
2024-03-21 sbl for of816: start of vt
2024-03-22 move nora reg addresses: SPI to the end, move RAMBMASK
2024-03-23 update bootrom to use new ROM/RAMBLOCK mapping
2024-03-23 cleanup ioregs-nora.md
2024-03-23 bus_controller: fix missing decode of sysregs on access from icd
2024-03-23 new sbl for the cx16 loading
2024-03-23 pbl: add the pre_loading callback
2024-03-24 icd: block cpu regs reading when IRQ enter sequence is detected
2024-03-24 cpuidec: make value width explicit in the prints
2024-03-24 sbl for cx16: update header table structure; add abrt02/isafix handler
2024-03-24 pcb: update the overview list of components with the current stock
2024-03-25 move sbl to common code
2024-03-25 move vera init to the sbl, convert to 65c02-only code (doh!)
2024-03-26 add a banner (X65.eu) to the sbl loading screen
2024-03-27 vt: implement putchar, with macros; has some problems...
2024-03-27 vt: fix priting; better but not 100% yet
2024-03-27 vt: add minimal cr-lf handling
2024-03-30 vt: add scroll and line clearing
2024-03-30 nora: disable ABRT02 mode on cpu reset always
2024-03-30 cpustep: check for stopped cpu
2024-03-30 icd: fix trace decode in the case ROMBLOCKs are disabled
2024-03-31 vt: the cursor is blinking on screen, some visual artifacts...
2024-04-01 icd: fix memory decode map in instruction trace prints
2024-04-01 vt: fix cursor blink video artefacts
2024-04-04 sbl: update of the banner text
2024-04-04 sbl: increase banner time to 3 sec
2024-04-04 vera: copy-in V47.0.2 from CX16 project; note: needs fix in bus_controller!!
    The commit:
    https://github.com/X16Community/vera-module/commit/fd78f273f2f05397f807115d08dedf5d267989cc
    Discussed here:
    https://github.com/X16Community/vera-module/pull/28
    arghh... Now the address setup margin for VERA is shorter, and it breaks our things.
    NORA must shift (delay) the write signal so that VERA sees correct address when WRn falls.
2024-04-05 nora bus_controller: fix vera timing: add 1cc delay on writes due to pull-28
2024-04-06 pic/of816-welcome.png
2024-04-06 of816: add initial kbd driver, works a bit
2024-04-10 x65-sbc-revB1 readme update with intentions
2024-04-13 nora: delaying vera_csn DOES NOT solve the timing issue, comment out
2024-04-13 nora: remove CPULED0 blinking
2024-04-18 of816 ps2: capslock led handling
2024-04-21 nora: i2c_master
2024-04-21 nora: upd i2c_master incl. ioregs description
2024-04-22 nora: integrate the i2c master
2024-04-23 do-i2cdump.py can dump RTC or EEPROM EUI data
2024-04-25 ps2 kbd handler: capslock/numlock/scrollock work
2024-10-06 doc: update links to tools
2024-11-26 add pcb/3dshapes step models
2025-01-02 new dbg.py: textual-based hw debugger app
2025-01-03 remove pcb/mobo - obsolete design
2025-01-03 remove pcb/vabo - obsolete design
